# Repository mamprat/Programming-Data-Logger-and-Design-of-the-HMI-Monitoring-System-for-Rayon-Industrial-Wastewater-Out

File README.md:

# Programming-Data-Logger-and-Design-of-the-HMI-Monitoring-System-for-Rayon-Industrial-Wastewater-Out

Monitoring waste water outlets is used to reduce environmental pollution loads and reduce 
the impact on human health that is influenced by the environment, using wastewater quality 
parameters that match quality standards. This concept of monitoring aims to facilitate 
workers in an industry especially in the of Waste Water Treatment Plant or WWTP to 
determine the temperature, pH and total suspended solid or TSS levels in waste water 
outlets in the rayon industry. In the testing of this monitoring system, the actual waste outlet 
environment is not used, but the testing is done by modeling the waste outlet while using 
waste water material samples from the rayon industry. The linear regression approach is 
used to analyze TSS levels in wastewater outlets in the rayon industry using Arduino Mega 
as a controller used to detect these parameters. The management of data from the 
monitoring is then stored in the data logger device as the data resulted fron the monitoring 
by storing the data in the form of time and quality detection results in wastewater and is 
integrated with HMI Nextion devices as the display and as a sensor offset settings from 
outlet of wastewater. The results of this monitoring will make it easier for workers to 
analyze the condition of waste water outlets and take countermeasures so as to reduce the 
pollution burden and reduce the impact on human health.

Key words : Arduino Mega, Data logger, Hmi Nextion

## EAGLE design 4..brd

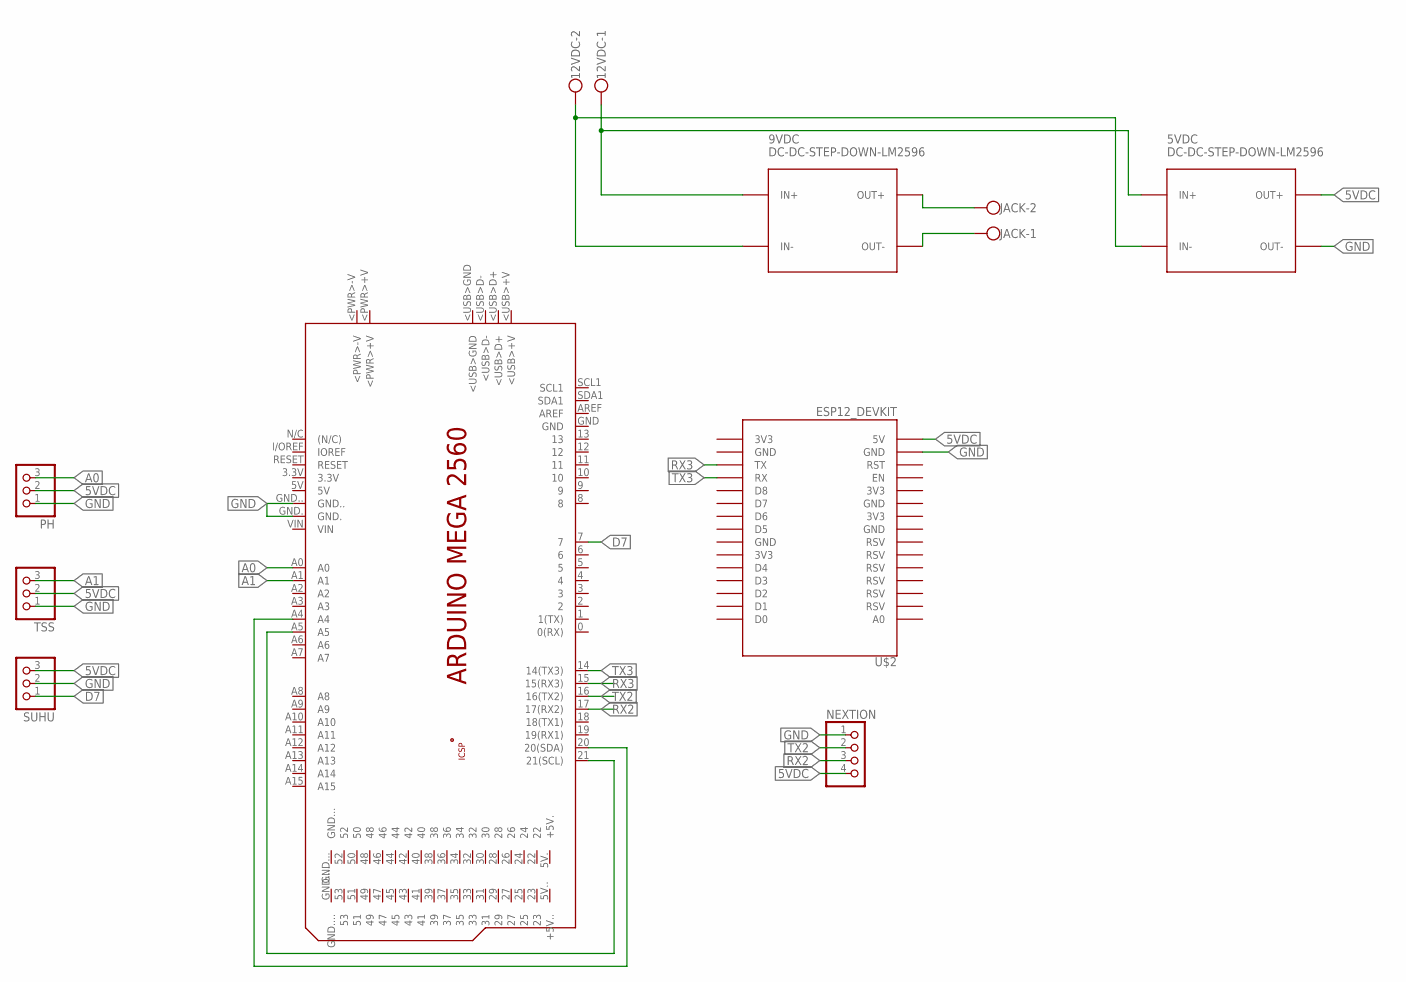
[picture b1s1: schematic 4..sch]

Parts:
5VDC, 9VDC: DC-DC-STEP-DOWN-LM2596
12VDC: W237-102
JACK: W237-102
NEXTION: PINHD-1X4; 1X04
PCB1: ARDUINO_MEGA2560
PH: PINHD-1X3; 1X03
SUHU: PINHD-1X3; 1X03
TSS: PINHD-1X3; 1X03
U$2: ESP12_DEVKIT

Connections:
5VDC: 5VDC.OUT+, NEXTION.4, PH.2, SUHU.3, TSS.2, U$2.5V
A0: PCB1.A0, PH.3
A1: PCB1.A1, TSS.3
D7: PCB1.7, SUHU.1
GND: 5VDC.OUT-, NEXTION.1, PCB1.GND., PCB1.GND.., PH.1, SUHU.2, TSS.1, U$2.GND@1 (GND)
unnamed: 5VDC.IN+, 9VDC.IN+, 12VDC.1
unnamed: 5VDC.IN-, 9VDC.IN-, 12VDC.2
unnamed: 9VDC.OUT+, JACK.2
unnamed: 9VDC.OUT-, JACK.1
unnamed: PCB1.20 (20(SDA)), PCB1.A4
unnamed: PCB1.21 (21(SCL)), PCB1.A5
RX2: NEXTION.3, PCB1.17 (17(RX2))
RX3: PCB1.15 (15(RX3)), U$2.TX
TX2: NEXTION.2, PCB1.16 (16(TX2))
TX3: PCB1.14 (14(TX3)), U$2.RX

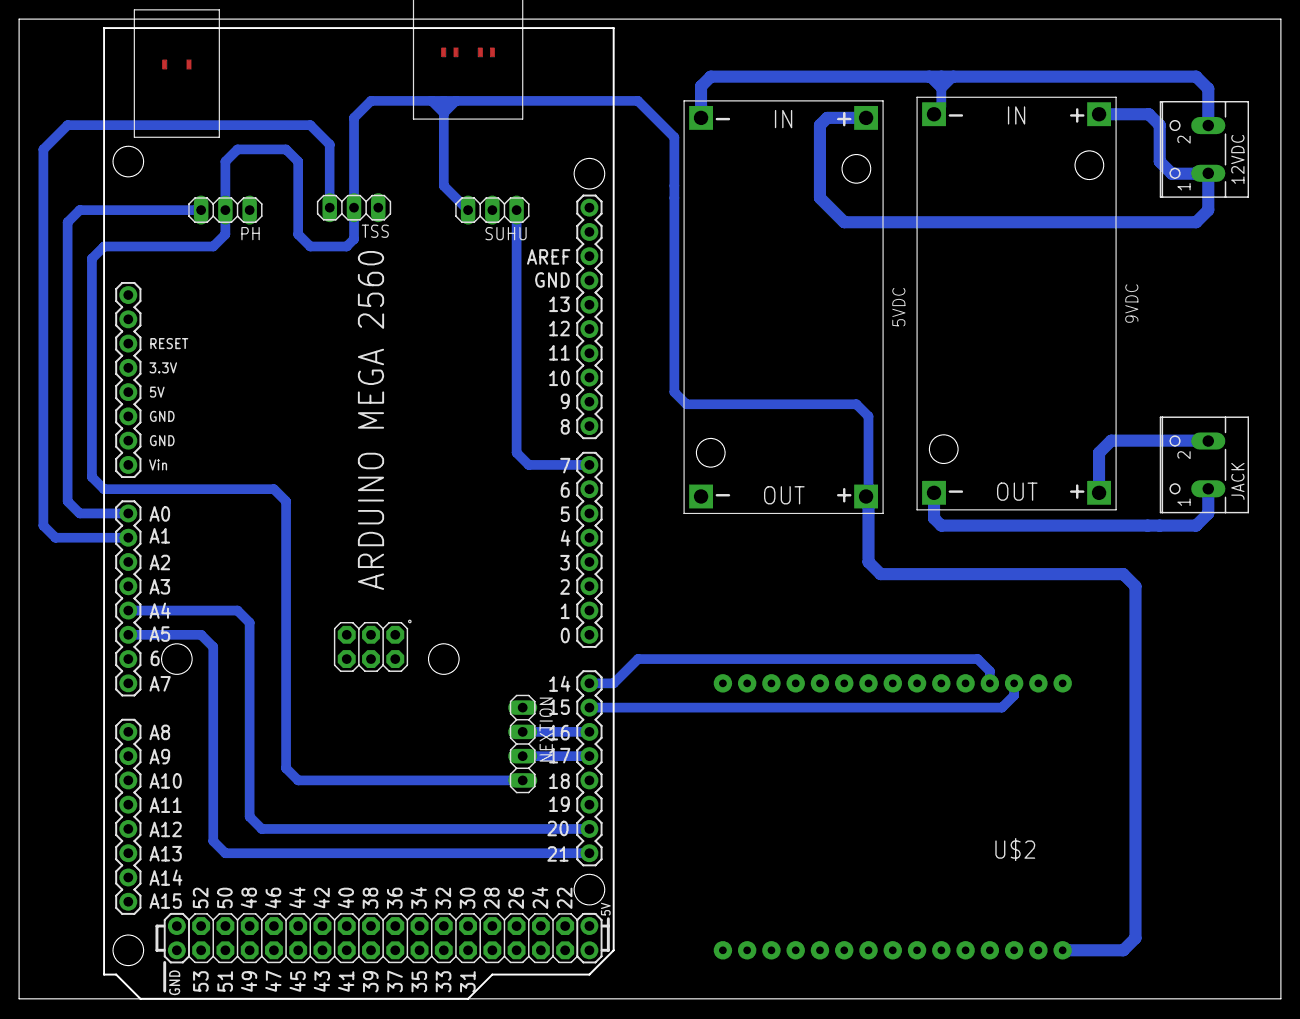
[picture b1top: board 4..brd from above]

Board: 2 copper layers, 132.1 x 102.5 mm, 10 parts (0 on the bottom side), 15 nets.

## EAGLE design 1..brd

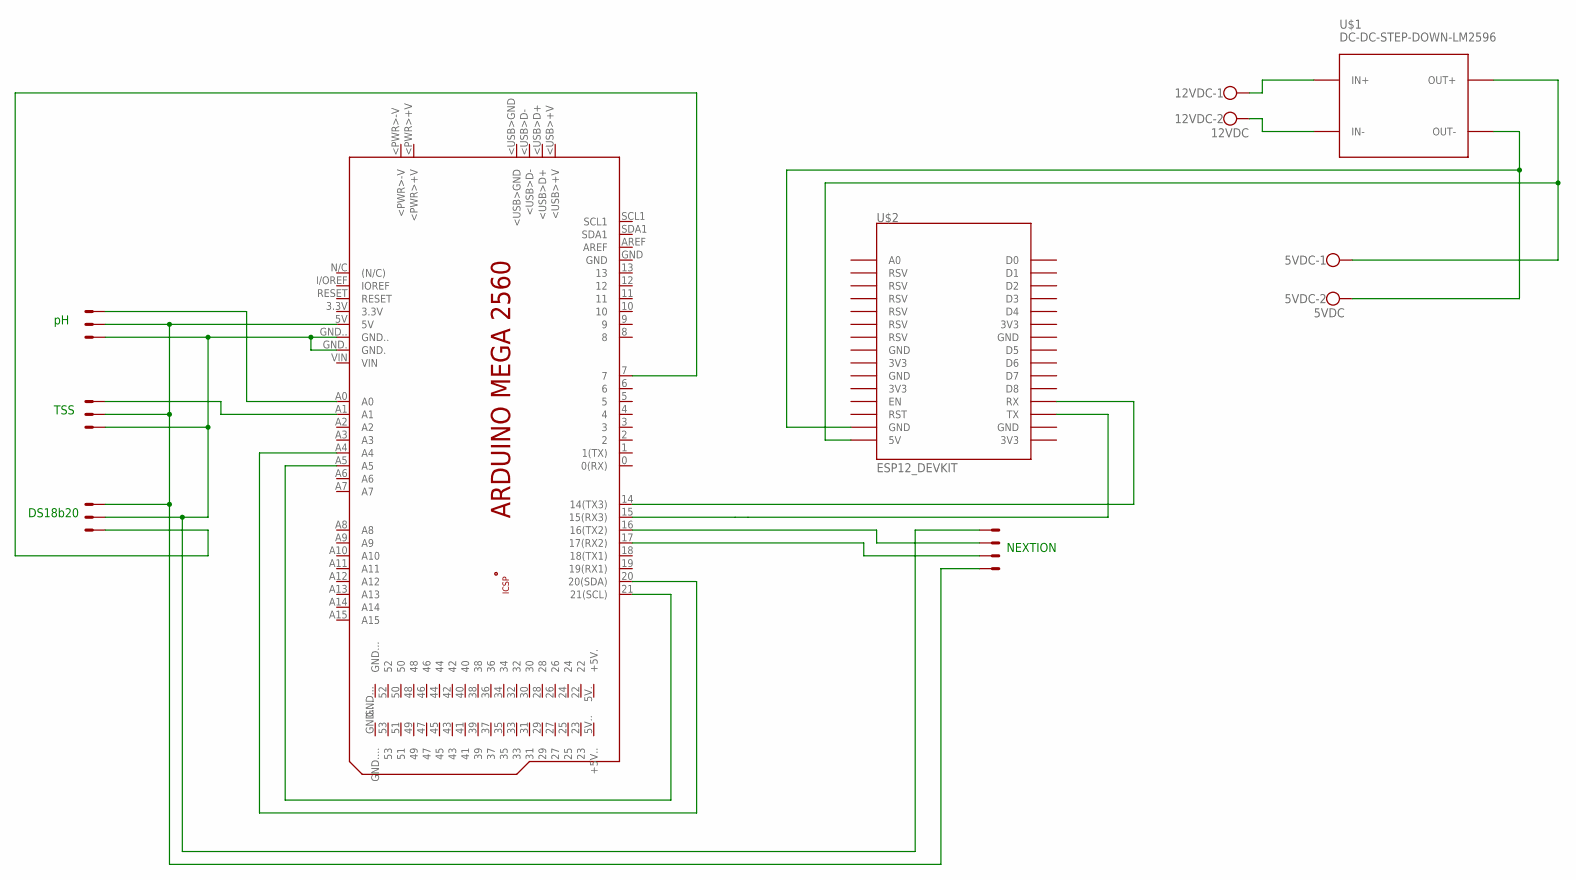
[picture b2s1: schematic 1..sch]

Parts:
5VDC: 5VDC; W237-102
12VDC: 12VDC; W237-102
A0: 22-23-2031
PCB1: ARDUINO_MEGA2560
U$1: DC-DC-STEP-DOWN-LM2596
U$2: ESP12_DEVKIT
X1: 22-23-2041
X2, X3: 22-23-2031

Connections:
unnamed: 12VDC.1, U$1.IN+
unnamed: 12VDC.2, U$1.IN-
unnamed: A0.1, PCB1.GND., PCB1.GND.., X1.1, X2.1, X3.2
unnamed: A0.2, PCB1.5V, X1.4, X2.2, X3.3
unnamed: A0.3, PCB1.A0
unnamed: PCB1.A1, X2.3
unnamed: PCB1.7, X3.1
unnamed: PCB1.20 (20(SDA)), PCB1.A4
unnamed: PCB1.21 (21(SCL)), PCB1.A5
unnamed: PCB1.14 (14(TX3)), U$2.RX
unnamed: PCB1.15 (15(RX3)), U$2.TX
unnamed: 5VDC.1, U$1.OUT+, U$2.5V
unnamed: 5VDC.2, U$1.OUT-, U$2.GND@1 (GND)
unnamed: PCB1.16 (16(TX2)), X1.2
unnamed: PCB1.17 (17(RX2)), X1.3

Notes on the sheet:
TSS
DS18b20
NEXTION

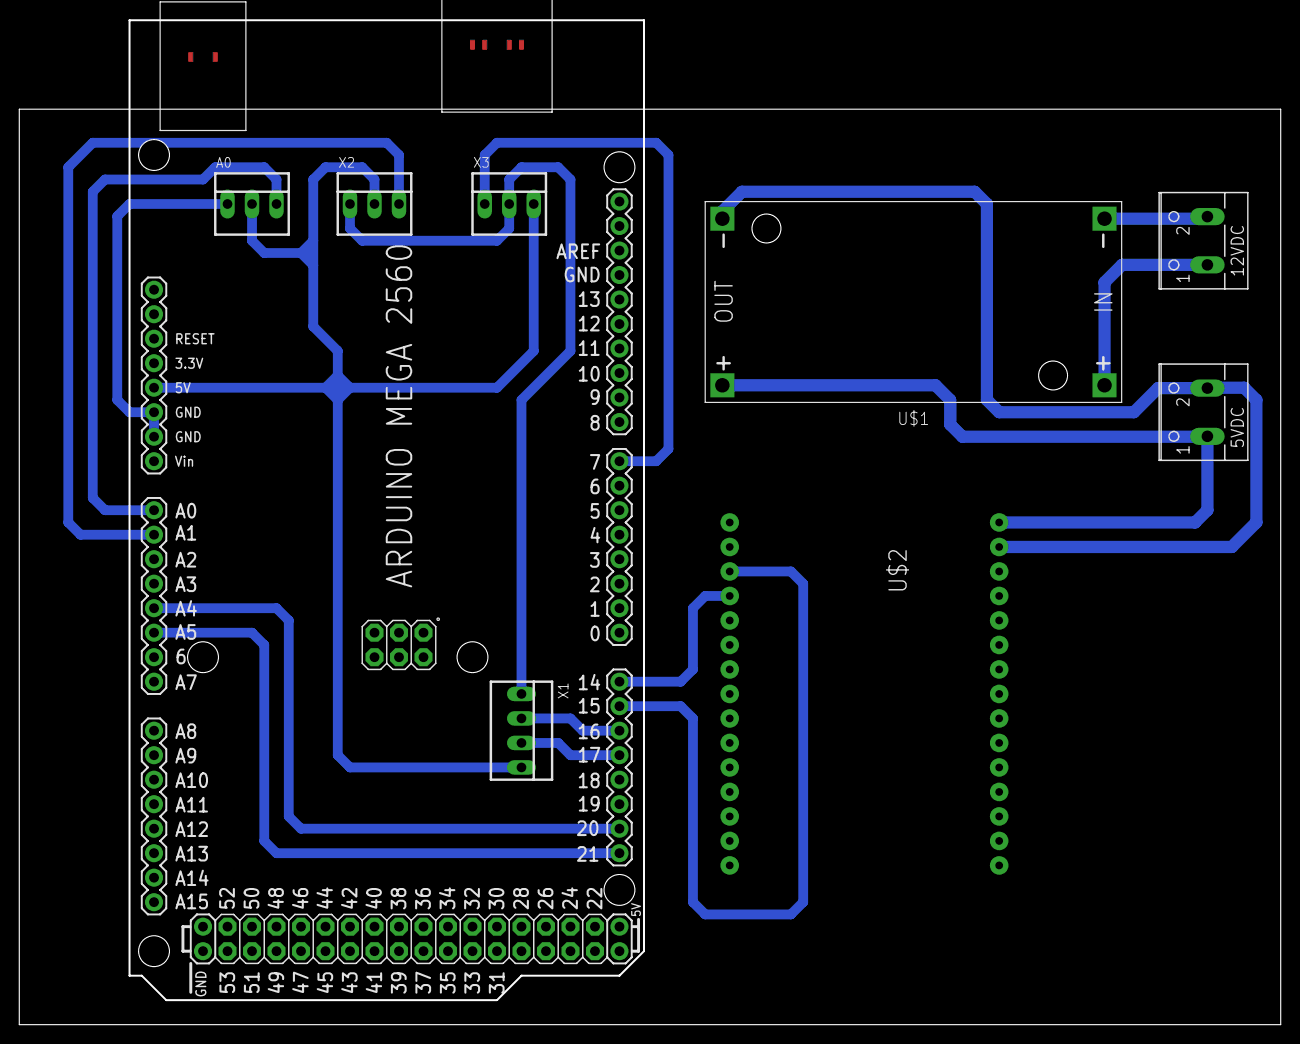
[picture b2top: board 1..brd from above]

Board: 2 copper layers, 130.8 x 104.1 mm, 9 parts (0 on the bottom side), 15 nets.

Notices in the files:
parts and their libraries:
diy-modules: Released under the Creative Commons Attribution 4.0 International License: http://creativecommons.org/licenses/by/4.0
